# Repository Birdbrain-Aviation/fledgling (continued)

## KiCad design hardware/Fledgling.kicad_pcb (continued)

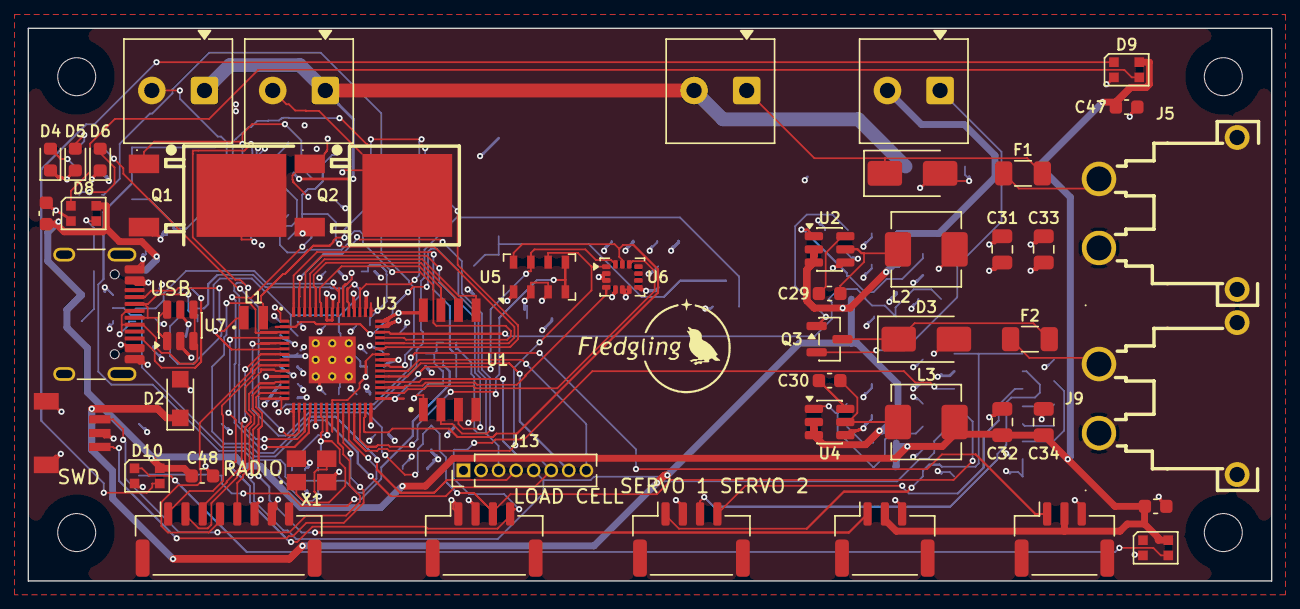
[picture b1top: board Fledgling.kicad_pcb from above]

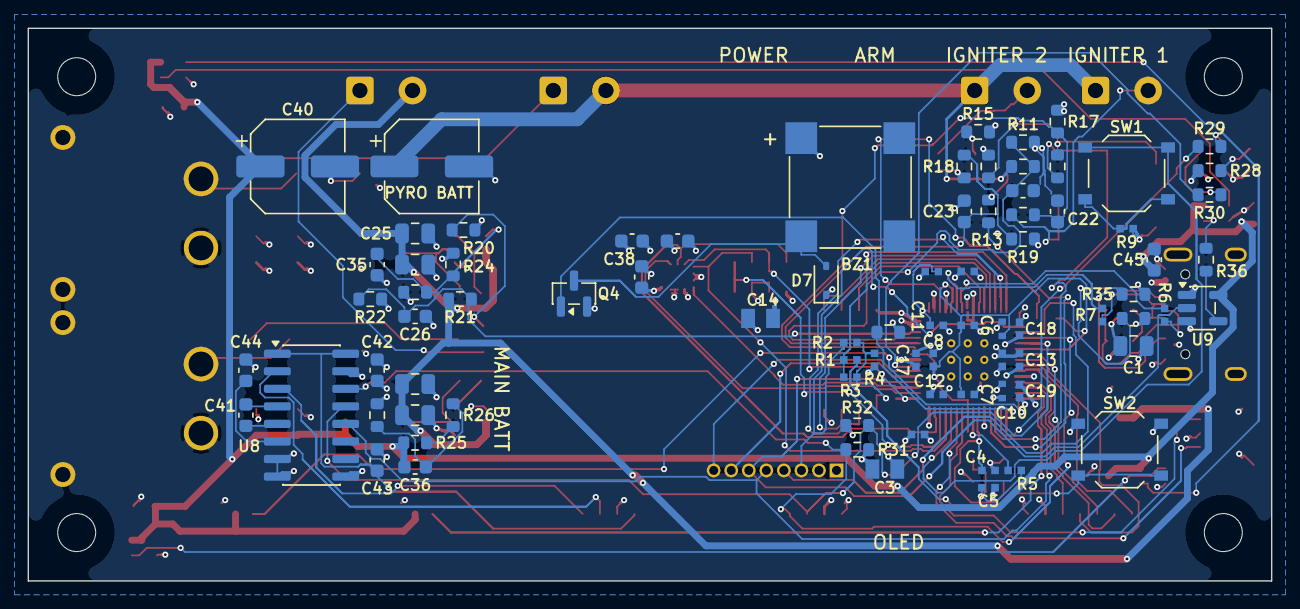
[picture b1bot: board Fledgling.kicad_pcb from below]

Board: 4 copper layers, 90.0 x 40.0 mm, 139 parts (83 on the bottom side), 92 nets.

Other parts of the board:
LBL1: Labels; Silk_Labels_Top
LBL2: Labels; Silk_Labels_Bottom
LOGO1: Fledgling_Logo; Fledgling_Logo_6.8mm

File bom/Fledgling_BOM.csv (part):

Boards to build,2,"Input. Change it and every Total qty and price below updates (radio, antenna, adapter, battery, cable and load cell rows have a fixed typed total). Set to 2 on 2026-11-13: PCBWay fabs 5 bare boards minimum but assembles as few as 1, so the plan is 5 bare / 2 assembled. Read the Flags & notes tab before ordering.",,,,,,,,,,,,
"Parts cost per board (priced rows, no spares)",$21.49,"Single board, on-board parts only. Optimistic LCSC 'from' prices; MOQs not included.",,,,,,,,,,,,
Order total for all boards + radios + batteries (priced rows),$114.95,"2 assembled boards plus 2 E220 radios, 2 antennas, the USB-serial adapter, one of each Tattu pack (shared with CORVID), the JST-GH cable parts and one load cell. PCB fab and assembly not included. NOTE: this is a floor, not the real bill. PCBWay's assembly minimums (0402 >=100 pcs and 50 over need; 0603/0805/1206/SOT/SOD >=50 and 30 over; 1-5 spares on ICs and connectors) push the parts cost to roughly $86-121 for 2 boards, i.e. an order total near $158-193. Ask PCBWay to return or shelf the leftovers - they are not returned by default.",,,,,,,,,,,,
,,,,,,,,,,,,,,
Reference group,Description,Manufacturer,MPN,LCSC number,Qty per board,Spares,Total qty to order,Unit price (USD),Extended price (USD),Price basis,Source URL,Stock,Status,Notes
MCU,"Flight MCU RP2350A, QFN-60 7x7, no internal flash [U3]",Raspberry Pi,RP2350A,C42411118,1,-,2,$1.0987,$2.20,Same part and price as the CORVID BOM (read 2026-11-03/04),https://www.lcsc.com/product-detail/C42411118.html,"4,934",verified (CORVID),"Same MCU family as CORVID, so drivers and flight code carry over."
Memory,Boot + log flash 128 Mbit QSPI [U1],Winbond,W25Q128JVSIQ,C97521,1,-,2,$1.5614,$3.12,Same part and price as the CORVID BOM (read 2026-11-03/04),https://www.lcsc.com/product-detail/C97521.html,8129,verified (CORVID),Program and flight log share this chip (16 MB is many flights at 100 Hz). Flash-write code must run from RAM.
Clock,"12 MHz crystal, 3225 [X1]",Abracon,ABM8-272-T3,C20625731,1,-,2,$0.3871,$0.77,Same part and price as the CORVID BOM (read 2026-11-03/04),https://www.lcsc.com/product-detail/C20625731.html,9380,verified (CORVID),MOQ 5. 15 pF load caps + 1 k series resistor per Raspberry Pi hardware guide.
Power,RP2350 core regulator inductor 3.3 uH (polarity marked) [L1],Abracon,AOTA-B201610S3R3-101-T,DigiKey 535-AOTA-B201610S3R3-101-TCT-ND,1,-,2,$0.2100,$0.42,"DigiKey 1-9 tier, read 2026-11-04 (CORVID BOM)",https://www.digikey.com/en/products/detail/abracon-llc/AOTA-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,"LCSC 0; DigiKey 14,076",verified (CORVID),Out of stock at LCSC: have PCBWay buy from DigiKey or consign it (buy CORVID's and Fledgling's together).
Sensor,"Barometer MS5611, 10-1200 mbar, SPI [U5]",TE Connectivity,MS561101BA03-50,C15639,1,-,2,$5.1127,$10.23,Same part and price as the CORVID BOM (read 2026-11-03/04),https://www.lcsc.com/product-detail/C15639.html,1026,verified (CORVID),Single baro. Use SPI0. Cover with foam over the vent hole against light and airflow.
Sensor,"6-axis IMU +/-32 g, +/-2000 dps, SPI [U6]",STMicroelectronics,LSM6DSO32TR,C1864162,1,-,2,$4.1602,$8.32,Same part and price as the CORVID BOM (read 2026-11-03/04),https://www.lcsc.com/product-detail/C1864162.html,22,verified (CORVID) - LOW STOCK,"Only 22 at LCSC on 2026-11-03 and CORVID also needs 5. Order both boards' worth together, soon."
Power,"Buck 3 A adjustable: U2 = 3.3 V logic, U4 = 5.0 V servo/radio/LED rail [U2, U4]",Diodes Inc,AP63301WU-7,C2158003,2,-,4,$0.6279,$2.51,Same part and price as the CORVID BOM (read 2026-11-03/04),https://www.lcsc.com/product-detail/C2158003.html,8904,verified (CORVID),"Same part twice = one footprint to learn. FB: 3.3 V = 31.6k/10k; 5.0 V = (47k+5.1k)/10k. Feed-forward caps across the FB top resistors: C35 560 pF (3.3 V) and C36 330 pF (5 V), both DNP footprints, scaled estimates from the datasheet value; tune on the bench."
Power,"Buck inductor 4.7 uH, Isat 5 A, 3.3 V rail [L2]",cjiang,FXL0530-4R7-M,C177246,1,-,2,$0.1268,$0.25,Same part and price as the CORVID BOM (read 2026-11-03/04),https://www.lcsc.com/product-detail/C177246.html,49415,verified (CORVID),
Power,"Buck inductor 6.8 uH, Isat 4 A, 5 V rail (datasheet value for 5 V out) [L3]",cjiang,FXL0530-6R8-M,C177249,1,-,2,$0.1205,$0.24,"LCSC 'from' price, read 2026-11-12",https://www.lcsc.com/product-detail/C177249.html,,,
Power,"Reverse-polarity P-FET, main battery [Q3]",UMW,AO3401A,C347476,1,-,2,$0.0352,$0.07,Same part and price as the CORVID BOM (read 2026-11-03/04),https://www.lcsc.com/product-detail/C347476.html,1357480,verified (CORVID),MOQ 20.
Pyro,"Pyro low-side N-FET, DPAK, 30 V [Q1, Q2]",Infineon,IRLR7843TRPBF,C21988,2,-,4,$0.7015,$2.81,"LCSC 10+ tier, read 2026-11-03 (CORVID BOM)",https://www.lcsc.com/product-detail/C21988.html,6009,verified (CORVID),Two pyro channels. Check Rds(on) at 3.3 V gate drive in the datasheet.
Audio,Buzzer driver N-FET [Q4],UMW,AO3400A,C347475,1,-,2,$0.0369,$0.07,Same part and price as the CORVID BOM (read 2026-11-03/04),https://www.lcsc.com/product-detail/C347475.html,1105580,verified (CORVID),MOQ 20.
Power,"Schottky, USB VBUS OR-ing [D2]",Nexperia,"PMEG2010ER,115",C82288,1,-,2,$0.1806,$0.36,Same part and price as the CORVID BOM (read 2026-11-03/04),https://www.lcsc.com/product-detail/C82288.html,14550,verified (CORVID),MOQ 5.
Protection,"TVS SMAJ9.0A on main and pyro inputs [D1, D3]",MDD,SMAJ9.0A,C113955,2,-,4,$0.0209,$0.08,Same part and price as the CORVID BOM (read 2026-11-03/04),https://www.lcsc.com/product-detail/C113955.html,1860,verified (CORVID),"Sized for 2S LiPo. If you ever use a 9 V battery on the pyro input, change D3 to SMAJ12A."
Audio,Buzzer flyback Schottky [D7],Guangdong Hottech,BAT54WS,C191198,1,-,2,$0.0063,$0.01,Same part and price as the CORVID BOM (read 2026-11-03/04),https://www.lcsc.com/product-detail/C191198.html,1800,verified (CORVID),
Protection,"Fast fuse 1206 3 A, main battery [F2]",Littelfuse,0466003.NRHF,C14165,1,-,2,$0.0594,$0.12,Same part and price as the CORVID BOM (read 2026-11-03/04),https://www.lcsc.com/product-detail/C14165.html,15410,verified (CORVID),
Protection,"Fast fuse 1206 5 A, pyro battery [F1]",Littelfuse,0466005.NRHF,C57525,1,-,2,$0.0359,$0.07,"LCSC 'from' price, read 2026-11-13. Sized for MJG Firewire Initiators: 1 ohm bridgewire, 0.6 A all-fire, so a 2S pack drives 6.4-7.3 A for 1-5 ms. Fuse melting I2t 2.5 A2s vs 0.27 A2s for one firing (0.98 even if both channels fire at once), so it passes the pulse but still opens on a sustained short - which the old 10 A placeholder would not.",https://www.lcsc.com/product-detail/C57525.html,13880,"decided, bench check pending","Keep 5 A, sized from the Firewire data: a fuse near 1 A would open on the 6-7 A firing pulse. Still to do: measure igniter current on the bench (Estes and nichrome igniters are not Firewire). Same 1206 footprint either way. MOQ 10."
USB,USB ESD protection [U7],STMicroelectronics,USBLC6-2SC6,C7519,1,-,2,$0.0932,$0.19,Same part and price as the CORVID BOM (read 2026-11-03/04),https://www.lcsc.com/product-detail/C7519.html,37330,verified (CORVID),
USB,USB-C receptacle 16-pin [J1],Korean Hroparts,TYPE-C-31-M-12,C165948,1,-,2,$0.0977,$0.20,Same part and price as the CORVID BOM (read 2026-11-03/04),https://www.lcsc.com/product-detail/C165948.html,155050,verified (CORVID),"Programming, log download, bench power. RP2350 native USB, no bridge chip."
Power,"XT30 PCB male, pyro and main batteries [J5, J9]",Changzhou Amass,XT30PW-M30.G.Y,C431092,2,-,4,$0.2273,$0.91,Same part and price as the CORVID BOM (read 2026-11-03/04),https://www.lcsc.com/product-detail/C431092.html,44260,verified (CORVID),"J3 (pyro) can be left unplugged on flights with no pyro, e.g. Emperor."
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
